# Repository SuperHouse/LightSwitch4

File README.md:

Home Automation Light Switch (4 Button)
========================================
Copyright 2014-2017 SuperHouse Automation Pty Ltd  
SuperHouse site:  <www.superhouse.tv>  

Illuminated push button breakout with an RJ45 socket, for mounting
in a wall panel as part of a home automation system.

Features:

 * 4 Illuminated push buttons
 * RJ45 breakout to allow connecting using Cat-5 cable

More information is available at:

  http://www.superhouse.tv/lightswitch

INSTALLATION
------------
The design is saved as an EAGLE project. EAGLE PCB design software is
available from www.cadsoftusa.com free for non-commercial use. To use
this project download it and place the directory containing these files
into the "eagle" directory on your computer. Then open EAGLE and
navigate to the project.

DISTRIBUTION
------------
The specific terms of distribution of this project are governed by the
license referenced below.

LICENSE
-------
Licensed under the TAPR Open Hardware License (www.tapr.org/OHL).
The "license" folder within this repository also contains a copy of
this license in plain text format.

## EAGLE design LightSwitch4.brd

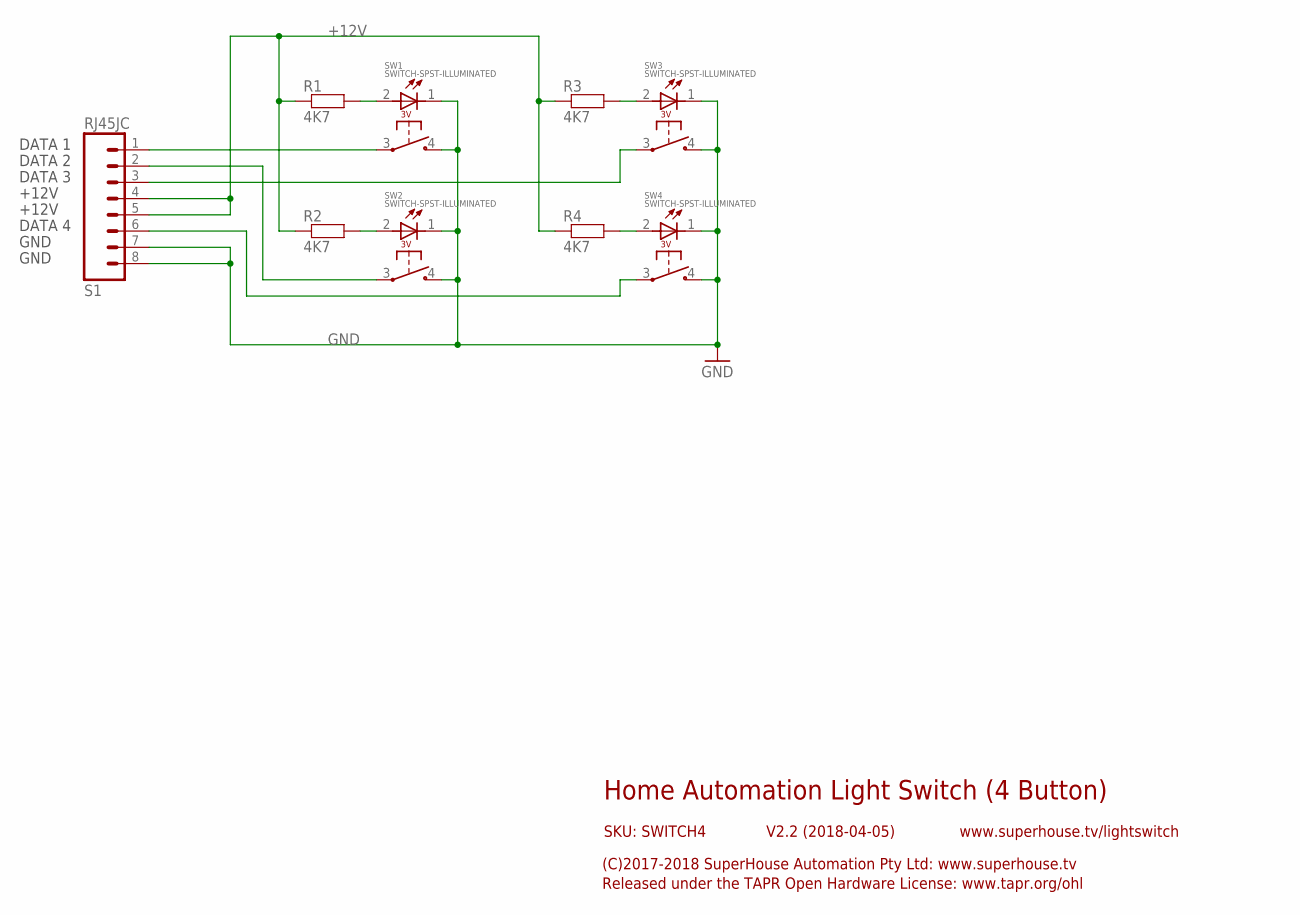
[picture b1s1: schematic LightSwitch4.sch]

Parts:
R1, R2, R3, R4: 4K7; 0603
S1: RJ45JC; RJ45
SW1, SW2, SW3, SW4: SWITCH-SPST-ILLUMINATED

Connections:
+12V: R1.1, R2.1, R3.1, R4.1, S1.4, S1.5
GND: S1.7, S1.8, SW1.1 (-), SW1.4 (NO), SW2.1 (-), SW2.4 (NO), SW3.1 (-), SW3.4 (NO), SW4.1 (-), SW4.4 (NO)
unnamed: R2.2, SW2.2 (+)
unnamed: S1.3, SW3.3 (COM)
unnamed: S1.6, SW4.3 (COM)
unnamed: S1.1, SW1.3 (COM)
unnamed: S1.2, SW2.3 (COM)
unnamed: R1.2, SW1.2 (+)
unnamed: R3.2, SW3.2 (+)
unnamed: R4.2, SW4.2 (+)

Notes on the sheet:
DATA 1
DATA 2
DATA 3
DATA 4
+12V
GND
Home Automation Light Switch (4 Button)
V2.2 (2018-04-05)
SKU: SWITCH4
(C)2017-2018 SuperHouse Automation Pty Ltd: www.superhouse.tv
Released under the TAPR Open Hardware License: www.tapr.org/ohl
www.superhouse.tv/lightswitch

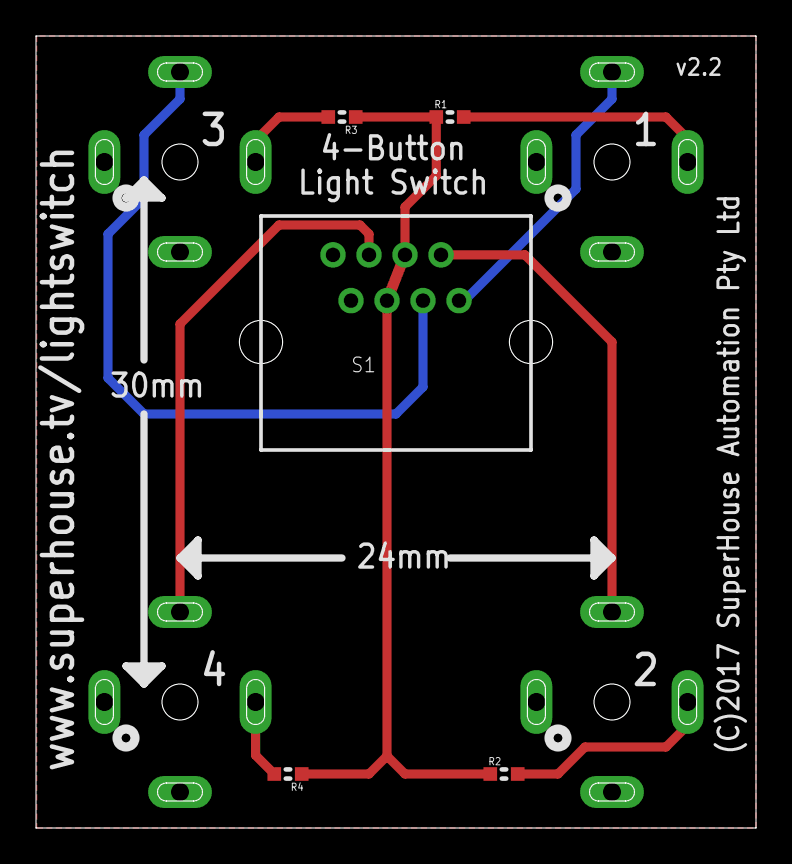
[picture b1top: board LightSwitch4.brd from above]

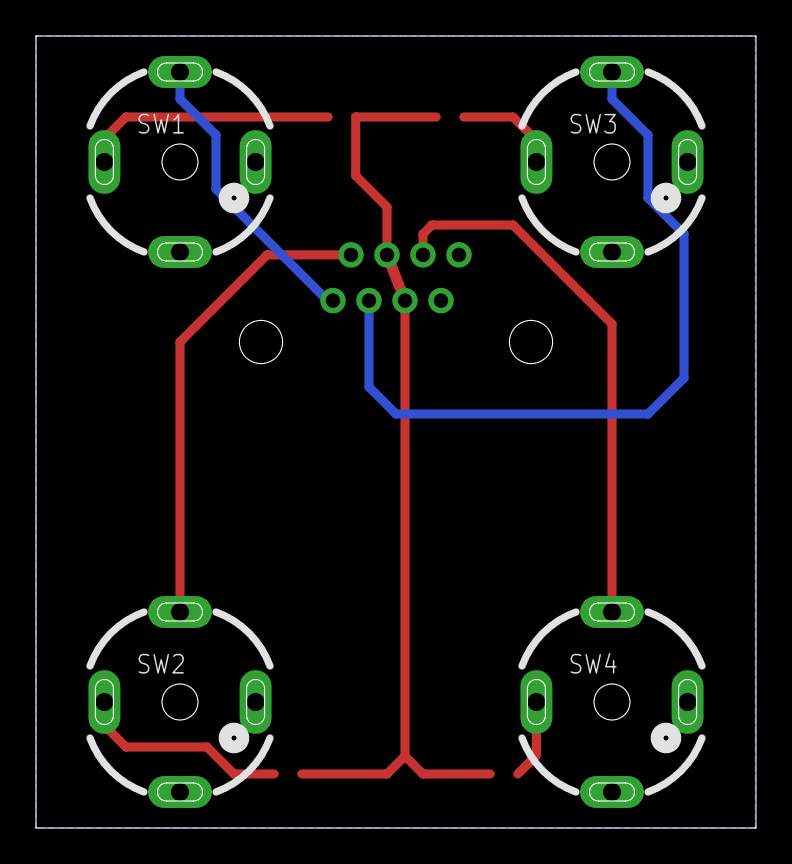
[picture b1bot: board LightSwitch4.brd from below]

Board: 2 copper layers, 40.0 x 44.0 mm, 9 parts (4 on the bottom side), 10 nets.

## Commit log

2017-10-07 Initial project import
2017-10-07 Improved labels for clarity
2017-10-07 Replaced buttons with more common SPST type
2017-10-12 Replaced buttons
2017-10-12 Renamed project files
2017-10-12 Updated README date
2018-03-26 Changed button footprint to slotted version for v2.1 release
2018-04-05 Updated RJ45 footprint for v2.2
2019-02-11 Release v2.2

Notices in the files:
LightSwitch4.brd:
(C)2017 SuperHouse Automation Pty Ltd
